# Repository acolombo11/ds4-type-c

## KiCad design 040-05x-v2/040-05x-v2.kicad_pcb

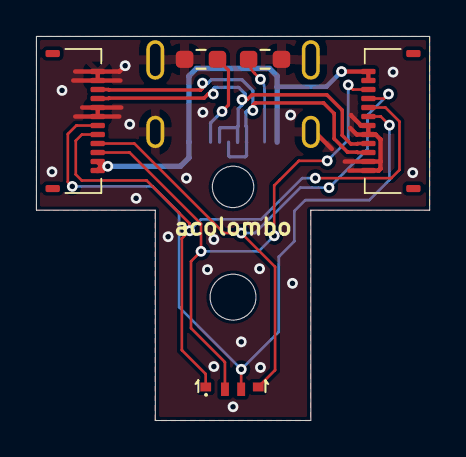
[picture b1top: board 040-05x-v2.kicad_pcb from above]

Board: 2 copper layers, 21.8 x 21.3 mm, 6 parts (1 on the bottom side), 10 nets.

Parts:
D1: LED_RAGB; FM-3510RGBA-SG
J2, J3: Conn_01x12; FPC_Connector
J4: USB_C_Receptacle_USB2.0_16P; USB_C
R3, R4: 5.1k; R_0603_1608Metric_Pad0.98x0.95mm_HandSolder

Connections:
+5V: J2.11, J2.12, J3.11, J3.12, J4.A4 (VBUS), J4.A9 (VBUS), J4.B4 (VBUS), J4.B9 (VBUS)
ANODE: D1.2 (A), J2.10, J3.10
BLUE: D1.4 (BK), J2.9, J3.9
GND: J2.1, J2.2, J2.5, J2.6, J3.1, J3.2, J3.5, J3.6, J4.A1 (GND), J4.A12 (GND), J4.B1 (GND), J4.B12 (GND), J4.S1 (SHIELD), R3.1, R4.2
GREEN: D1.3 (GK), J2.7, J3.7
unnamed: J4.A5 (CC1), R4.1
unnamed: J4.B5 (CC2), R3.2
RED: D1.1 (RK), J2.8, J3.8
USBD+: J2.3, J3.3, J4.A6 (D+), J4.B6 (D+)
USBD-: J2.4, J3.4, J4.A7 (D-), J4.B7 (D-)

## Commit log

2024-08-09 Add my own logo
